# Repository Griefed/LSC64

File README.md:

# **This is still a WIP**

# **This is still a WIP**

# Sources, GitHub, GitLab and Mirroring and all that good stuff

Repositories on GitHub are now for issues only. I've set up my own installation of GitLab and moved all my repositories over to [Git.Griefed.de](https://git.griefed.de/users/Griefed/projects). Make sure to check there first for the latest code before opening an issue on GitHub.

For questions, you can always join my [Discord server](https://discord.griefed.de) and talk to me there.

---

[[_TOC_]]

**This has yet to be tested IRL. I currently don't have the funds to procure the PCB and parts in order to build and test it. No guarantee on anything as of yet. Also, the code for the Attiny85 has yet to be written, reason: See above.**
----
## Features

A PCB to enhance your C64C with various things:
- A Larson Scanner with RGB LEDs, so you can configure it to your liking!
- An Expansion Port reset circuit. You just need to connect a button and off you go!
- A CPU brake: Throttle your CPU and slow down your game during the really tricky bits!
- Mono & Stereo Headphone Amp. Listen to the beautiful SID sounds with your headphones. Either in mono or in stereo, if you have an FPGA SID!

## Assembly

After getting the PCB printed the the printing service of your choice and getting all the parts from the vendor of your choice, take a good look at [the interactive BOM](BOMinteractive.html).
It's a nice interactive overview of the whole PCB, which helps you placing all your parts where they're supposed to be! (You need to download )
Thanks to the Open Scope Project on GitHub for this amazing KiCad plugin: [InteractiveHtmlBom](https://github.com/openscopeproject/InteractiveHtmlBom)

## Connecting your LSC64

### Larson Scanner

For information about the pin layout of the power connector, check out: [C64 Power Supply Connector](https://www.c64-wiki.com/wiki/Power_Supply_Connector)

The bottom 3 pins of J1 to J20 are all the same. The top 3 pins of J1 to J20 represent one colour of the RGB LED each.
From left to right: red, blue green.
So, to set the colours of the LED:

| From                  | Of                   | To                        | Of                                                                                | Colour |
|:----------------------|:--------------------:|:-------------------------:|----------------------------------------------------------------------------------:|:------:|
| Any of J21            | LSC64                | Pin 5 (+5V DC)            | [C64 Power Supply Connector](https://www.c64-wiki.com/wiki/Power_Supply_Connector)| -x-    |
| Any of J21            | LSC64                | J24                       | LSC64                                                                             | -x-    |
| Any of J26            | LSC64                | Pin 2 (GND)               | [C64 Power Supply Connector](https://www.c64-wiki.com/wiki/Power_Supply_Connector)| -x-    |
| J1 to J20 - Bottom Row| LSC64                | J1 to J20 - Top Left      | LSC64                                                                             | Red    |
| J1 to J20 - Bottom Row| LSC64                | J1 to J20 - Top Middle    | LSC64                                                                             | Blue   |
| J1 to J20 - Bottom Row| LSC64                | J1 to J20 - Top Right     | LSC64                                                                             | Green  |

**Caution: Enabling more than one colour may result in the LED not lighting up at all. That is due to the output capacity of the Attiny85.**

**I recommend you only have one colour per LED enabled at all times.**

Special thanks to Luc Volders for the explanations and examples on how to build a charlieplexed Larson Scanner: [Luc's Tech Blog post about his Larson Scanner](https://lucstechblog.blogspot.com/2017/09/charlieplexing.html)

### The Reset Button

| From          | Of                   | To                        | Of                                                                                                      |
|:--------------|:--------------------:|:-------------------------:|--------------------------------------------------------------------------------------------------------:|
| J22           | LSC64                | Pin C (RESET)             | [C64 Expansion Port](https://www.c64-wiki.com/wiki/Expansion_Port)                                      |
| J27           | LSC64                | Pin 9 (EXROM)             | [C64 Expansion Port](https://www.c64-wiki.com/wiki/Expansion_Port)                                      |
| J23           | LSC64                | Pin 1                     | [Button](https://www.digikey.de/product-detail/de/e-switch/RP3502MABLK/EG1932-ND/280450?cur=EUR&lang=de)|
| Any of J26    | LSC64                | Pin 2                     | [Button](https://www.digikey.de/product-detail/de/e-switch/RP3502MABLK/EG1932-ND/280450?cur=EUR&lang=de)|

Special thanks to AntaBaka for the schematics and the idea: [Expansionport-Deluxe-Reset](http://pitsch.de/stuff/c64/index_c64.htm#A24)

### CPU Brake

| From          | Of                   | To                        | Of                                                                |
|:--------------|:--------------------:|:-------------------------:|------------------------------------------------------------------:|
| Pin 1         | On/Off Switch        | J21                       | LSC64                                                             |
| Pin 2         | On/Off Switch        | J24                       | LSC64                                                             |
| Terminal 1    | Dual Potentiometer   | Right Pin R29             | LSC64                                                             |
| Terminal 2    | Dual Potentiometer   | Middle Pin R29            | LSC64                                                             |
| Terminal 3    | Dual Potentiometer   | Left Pin R29              | LSC64                                                             |
| J25           | LSC64                | Pin 4 (IRQ)               | [C64 Expansion Port](https://www.c64-wiki.com/wiki/Expansion_Port)|

Special thanks to AntaBaka for the schematics and the idea: [CPU Brake NE555](http://pitsch.de/stuff/c64/index_c64.htm#A41)

### Mono-Stereo Headphone examples

##### CAUTION
- **Boards with assembly no. 250469 have no VR1. Check beforehand!**
- **Stereo sound REQUIRES an [FPGA SID](https://webstore.kryoflux.com/catalog/product_info.php?cPath=27&products_id=63&language=en)!**

| From          | Of                   | To                        | Of                                                         |
|:--------------|:--------------------:|:-------------------------:|-----------------------------------------------------------:|
| J31           | LSC64                | Pin 7 & 9                 | Rotary Switch                                              |
| J29           | LSC64                | Pin 2                     | Dual Potentiometer                                         |
| J35           | LSC64                | Pin 12                    | Rotary Switch                                              |
| J36           | LSC64                | Pin 5                     | Dual Potentiometer                                         |
| Pin 15 & 16   | Rotary Switch        | Pin 2                     | [VR1](images/Amp_Power_Supply.PNG)                         |
| Pin 1         | Dual Potentiometer   | Pin 3 (AUDIO_OUT)         | [C64 A/V connector](https://www.c64-wiki.com/wiki/A/V_Jack)|
| Pin 4         | Dual Potentiometer   | Pin 7 (FPGA SID AUDIO OUT)| [C64 A/V connector](https://www.c64-wiki.com/wiki/A/V_Jack)|
| Pin 3 & 6     | Dual Potentiometer   | Any of J26                | LSC64                                                      |
| J32           | LSC64                | Pin 13                    | Rotary Switch                                              |
| J38           | LSC64                | Pin 14                    | Rotary Switch                                              |
| Pin 1         | Rotary Switch        | Pin 2 (Tip) & Pin 3 (Ring)| Headphone Jack Mono                                        |
| Pin 1 (Sleeve)| Headphone Jack Mono  | Any of J26                | LSC64                                                      |
| Pin 3         | Rotary Switch        | Pin 2 (Tip)               | Headphone Jack Stereo                                      |
| Pin 6         | Rotary Switch        | Pin 3 (Ring)              | Headphone Jack Stereo                                      |
| Pin 1 (Sleeve)| Headphone Jack Stereo| Any of J26                | LSC64                                                      |

**Additional parts required but not listed in the InteractiveHtmlBom (They're not a physical part of the LSC64 PCB)**
- **4x3 rotary switch** (e.g.:[Symbol](images/Rotary_Switch4x3.PNG), [Datasheet Model A403](https://dznh3ojzb2azq.cloudfront.net/products/Rotary/A/documents/datasheet.pdf), [Product page](https://www.digikey.de/product-detail/de/c-k/A40315RNZQ/CKC7008-ND/181440)).
- **dual potentiometer to change the volume** (e.g.:[Symbol](images/Dual_Potentiometer.PNG), [Datasheet](https://www.bourns.com/docs/Product-Datasheets/PDB18.pdf), [Product page](https://www.digikey.de/product-detail/de/bourns-inc/PDB182-K430K-104A/PDB182-K430K-104A-ND/3780721)).
- **Audio jack to plug in your headphones** (e.g.: [Datasheet](https://us.schurter.com/bundles/snceschurter/epim/_ProdPool_/newDS/en/typ_4832.2300.pdf), [Product page](https://www.digikey.de/product-detail/de/schurter-inc/4832-2300/486-3419-ND/1731055)).

Special thanks to AntaBaka for the schematics and the idea [Headphone Amp Mono](http://pitsch.de/stuff/c64/index_amp.htm) and Minidisc.org for the stereo schematics [HeadBanger Headphone Amp](http://www.minidisc.org/headbanger.html)

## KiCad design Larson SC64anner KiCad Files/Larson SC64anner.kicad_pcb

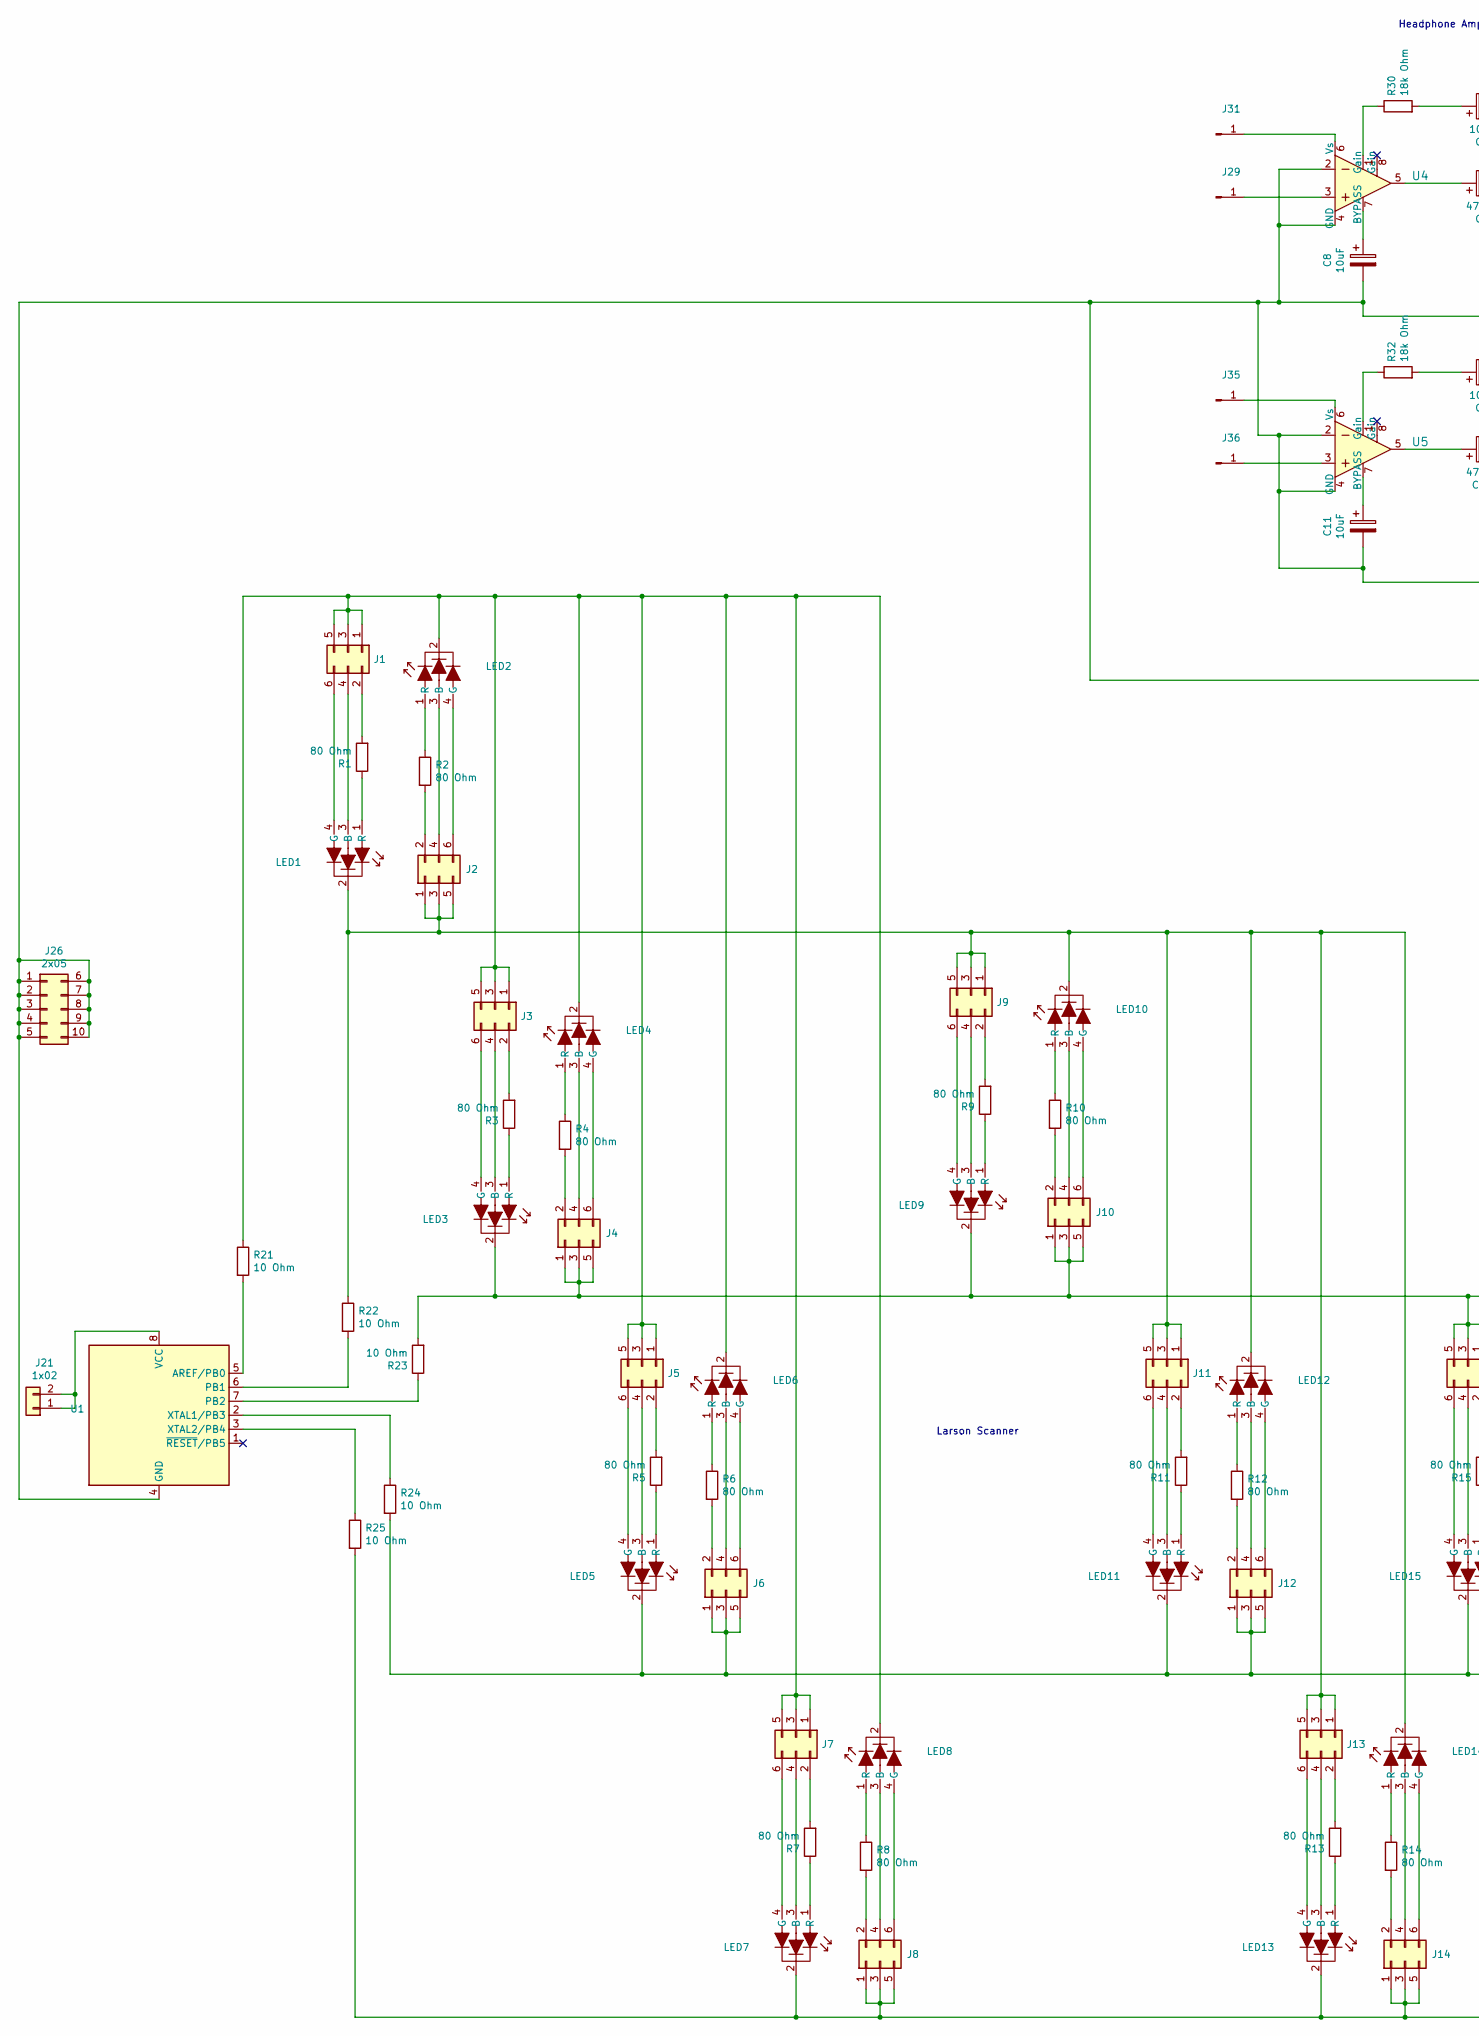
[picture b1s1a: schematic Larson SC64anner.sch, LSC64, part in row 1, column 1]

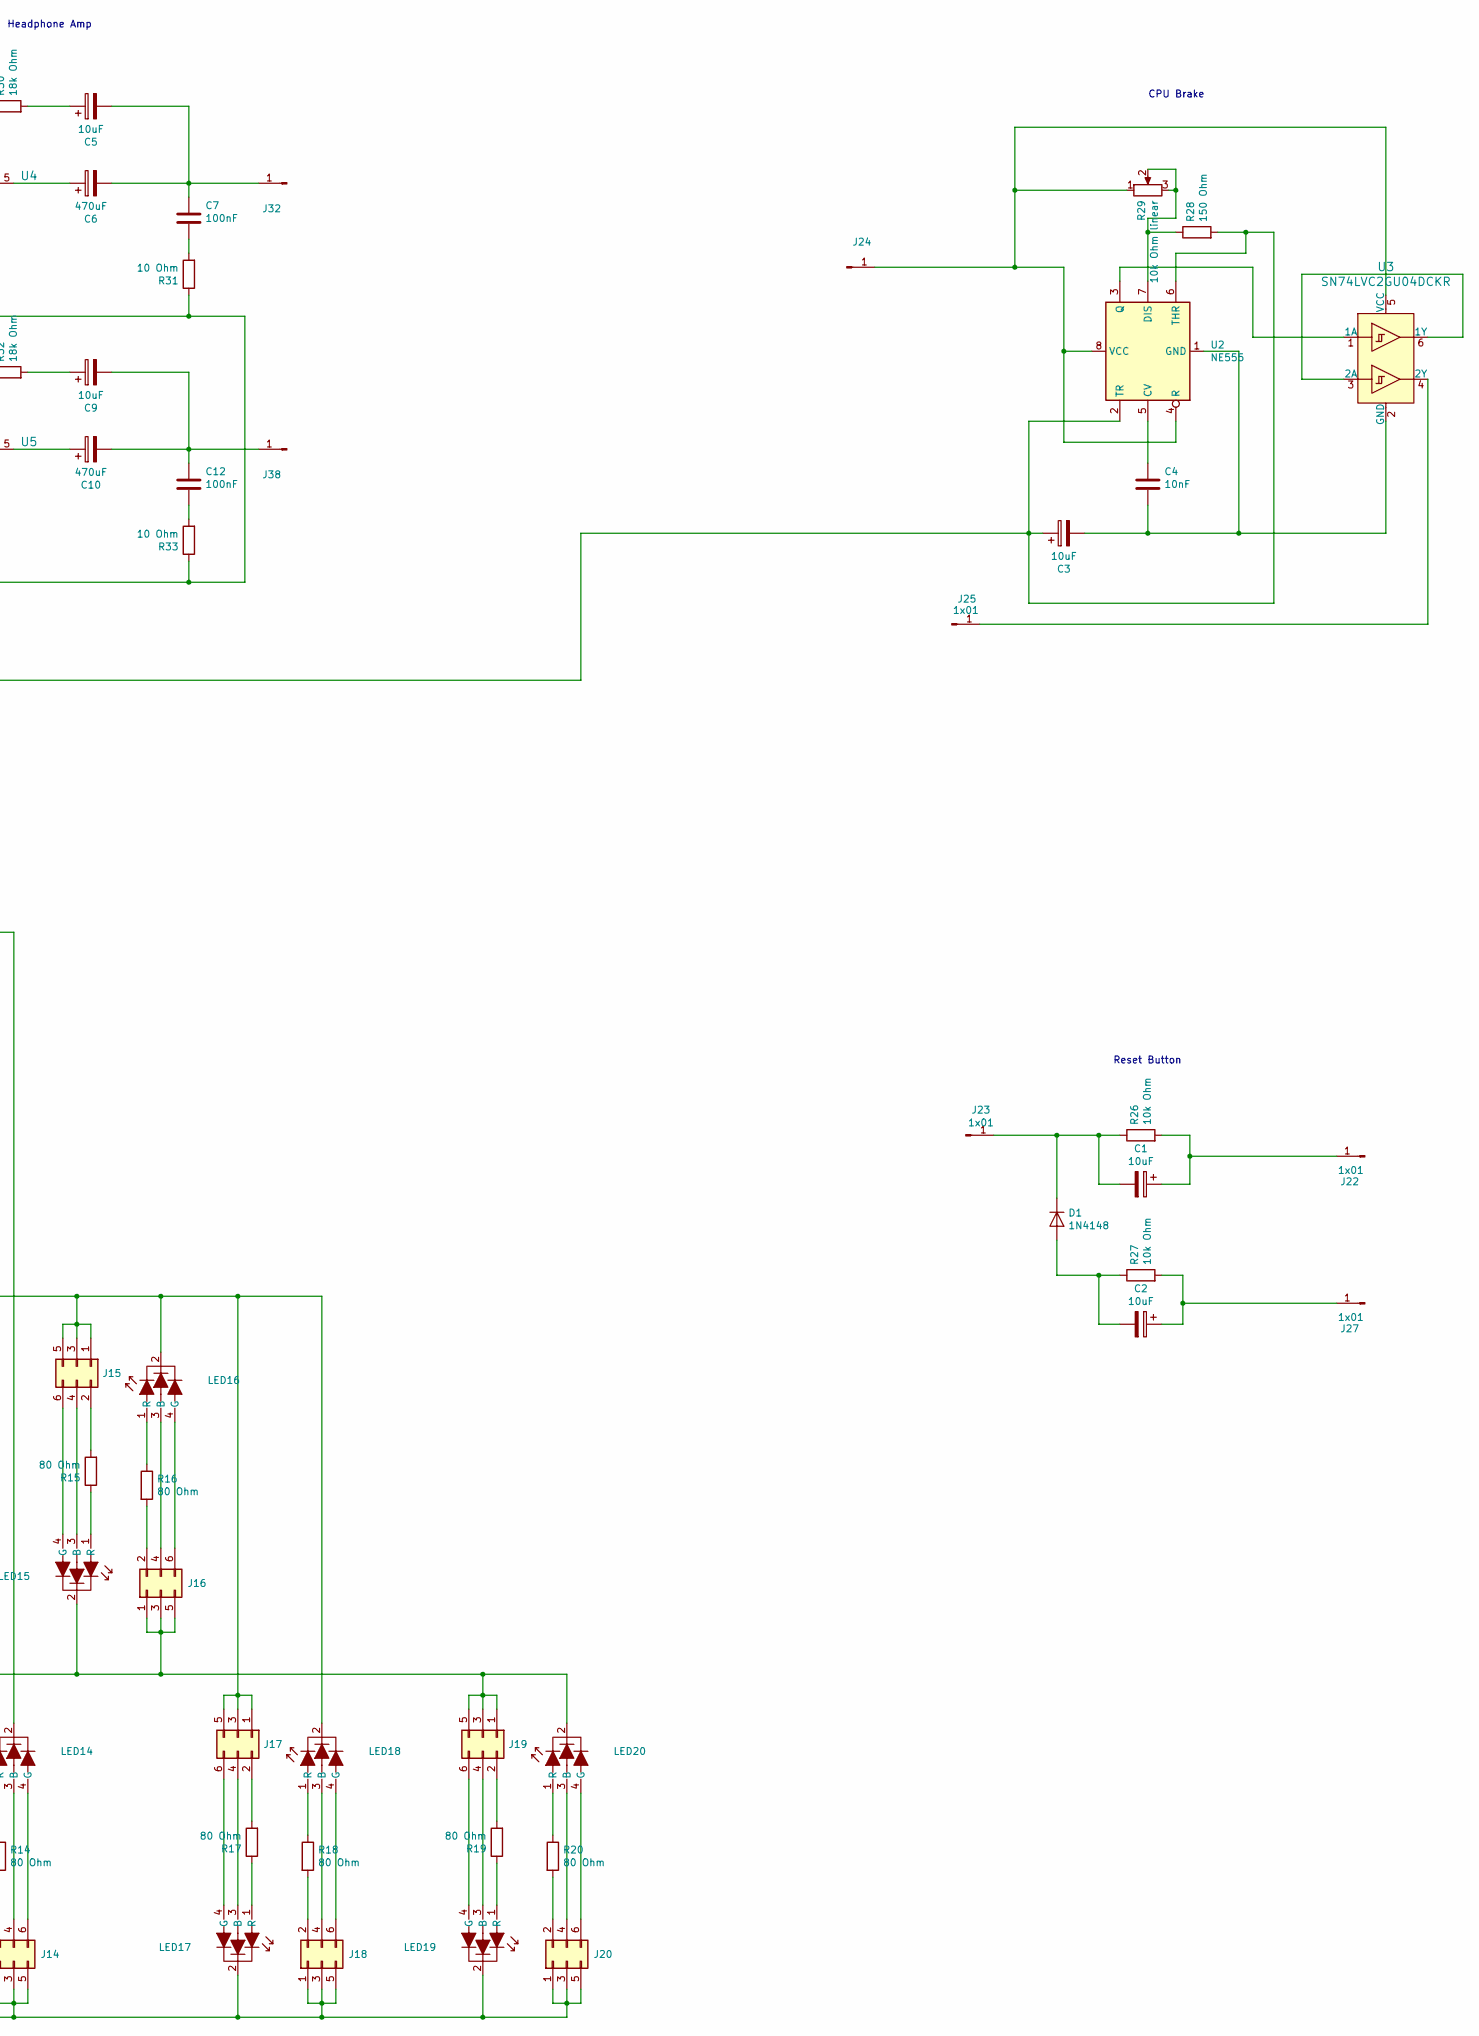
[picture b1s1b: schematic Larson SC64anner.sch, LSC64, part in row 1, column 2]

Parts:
C1, C2, C3, C5, C8, C9, C11: 10uF; CP_Radial_D5.0mm_P2.50mm
C4: 10nF; C_Disc_D7.5mm_W2.5mm_P5.00mm
C6, C10: 470uF; CP_Radial_D5.0mm_P2.50mm
C7, C12: 100nF; C_Disc_D7.5mm_W2.5mm_P5.00mm
D1: 1N4148; D_DO-35_SOD27_P7.62mm_Horizontal
J1, J2, J3, J4, J5, J6, J7, J8, J9, J10, J11, J12, J13, J14, J15, J16, J17, J18, J19, J20: 2x03; PinHeader_2x03_P2.54mm_Vertical
J21: 1x02; PinHeader_1x02_P2.54mm_Vertical
J22, J23, J24, J25, J27, J29, J31, J32, J35, J36, J38: 1x01; PinHeader_1x01_P2.54mm_Vertical
J26: 2x05; PinHeader_2x05_P2.54mm_Vertical
LED1, LED2, LED3, LED4, LED5, LED6, LED7, LED8, LED9, LED10, LED11, LED12, LED13, LED14, LED15, LED16, LED17, LED18, LED19, LED20: LED_CRGB; LED_RGB_WP154A4SUREQBFZGC
R1, R2, R3, R4, R5, R6, R7, R8, R9, R10, R11, R12, R13, R14, R15, R16, R17, R18, R19, R20: 80 Ohm; R_Axial_DIN0207_L6.3mm_D2.5mm_P2.54mm_Vertical_reduced_cour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
R21, R22, R23, R24, R25, R31, R33: 10 Ohm; R_Axial_DIN0207_L6.3mm_D2.5mm_P2.54mm_Vertical_reduced_cour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
R26, R27: 10k Ohm; R_Axial_DIN0207_L6.3mm_D2.5mm_P2.54mm_Vertical_reduced_cour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
R28: 150 Ohm; R_Axial_DIN0207_L6.3mm_D2.5mm_P2.54mm_Vertical_reduced_cour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
R29: 10k Ohm linear; PinHeader_1x03_P2.54mm_Vertical
R30, R32: 18k Ohm; R_Axial_DIN0207_L6.3mm_D2.5mm_P2.54mm_Vertical_reduced_cour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
U1: ATtiny85V-20PU; DIP-8_W7.62mm
U2: NE555; DIP-8_W7.62mm
U3: SN74LVC2GU04DCKR; SMDIP-6_W7.62mm
U4, U5: LM386N-4_NOPB; DIP-8_W7.62mm; MPN LM386N-4/NOPB; Digi-Key_PN 296-43960-5-ND

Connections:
unnamed: C1.1, J22.1, R26.2
unnamed: C1.2, D1.1 (K), J23.1, R26.1
unnamed: C2.1, J27.1, R27.2
unnamed: C2.2, D1.2 (A), R27.1
unnamed: C3.2, C4.2, U2.1 (GND), U3.2 (GND)
unnamed: C4.1, U2.5 (CV)
unnamed: C5.1, R30.2
unnamed: C5.2, C6.2, C7.1, J32.1
unnamed: C6.1, U4.5
unnamed: C7.2, R31.2
unnamed: C8.1, U4.7 (BYPASS)
unnamed: C9.1, R32.2
unnamed: C10.1, U5.5
unnamed: C9.2, C10.2, C12.1, J38.1
unnamed: C11.1, U5.7 (BYPASS)
unnamed: C3.1, C8.2, C11.2, J26.1, J26.2, J26.3, J26.4, J26.5, J26.6, J26.7, J26.8, J26.9, J26.10, R28.2, R31.1, R33.1, U1.4 (GND), U2.2 (TR), U2.6 (THR), U4.2, U4.4 (GND), U5.2, U5.4 (GND)
unnamed: C12.2, R33.2
unnamed: J1.1, J1.3, J1.5, J3.1, J3.3, J3.5, J5.1, J5.3, J5.5, J7.1, J7.3, J7.5, LED2.2, LED4.2, LED6.2, LED8.2, R21.1
unnamed: J1.2, R1.2
unnamed: J1.4, LED1.3 (B)
unnamed: J1.6, LED1.4 (G)
unnamed: J2.2, R2.2
unnamed: J2.4, LED2.3 (B)
unnamed: J2.6, LED2.4 (G)
unnamed: J3.2, R3.2
unnamed: J3.4, LED3.3 (B)
unnamed: J3.6, LED3.4 (G)
unnamed: J4.2, R4.2
unnamed: J4.4, LED4.3 (B)
unnamed: J4.6, LED4.4 (G)
unnamed: J5.2, R5.2
unnamed: J5.4, LED5.3 (B)
unnamed: J5.6, LED5.4 (G)
unnamed: J6.2, R6.2
unnamed: J6.4, LED6.3 (B)
unnamed: J6.6, LED6.4 (G)
unnamed: J7.2, R7.2
unnamed: J7.4, LED7.3 (B)
unnamed: J7.6, LED7.4 (G)
unnamed: J8.2, R8.2
unnamed: J8.4, LED8.3 (B)
unnamed: J8.6, LED8.4 (G)
unnamed: J9.2, R9.2
unnamed: J9.4, LED9.3 (B)
unnamed: J9.6, LED9.4 (G)
unnamed: J4.1, J4.3, J4.5, J10.1, J10.3, J10.5, J15.1, J15.3, J15.5, J17.1, J17.3, J17.5, LED3.2, LED9.2, LED16.2, LED18.2, R23.2
unnamed: J10.2, R10.2
unnamed: J10.4, LED10.3 (B)
unnamed: J10.6, LED10.4 (G)
unnamed: J2.1, J2.3, J2.5, J9.1, J9.3, J9.5, J11.1, J11.3, J11.5, J13.1, J13.3, J13.5, LED1.2, LED10.2, LED12.2, LED14.2, R22.1
unnamed: J11.2, R11.2
unnamed: J11.4, LED11.3 (B)
unnamed: J11.6, LED11.4 (G)
unnamed: J6.1, J6.3, J6.5, J12.1, J12.3, J12.5, J16.1, J16.3, J16.5, J19.1, J19.3, J19.5, LED5.2, LED11.2, LED15.2, LED20.2, R24.2
unnamed: J12.2, R12.2
unnamed: J12.4, LED12.3 (B)
unnamed: J12.6, LED12.4 (G)
unnamed: J13.2, R13.2
unnamed: J13.4, LED13.3 (B)
unnamed: J13.6, LED13.4 (G)
unnamed: J8.1, J8.3, J8.5, J14.1, J14.3, J14.5, J18.1, J18.3, J18.5, J20.1, J20.3, J20.5, LED7.2, LED13.2, LED17.2, LED19.2, R25.2
unnamed: J14.2, R14.2
unnamed: J14.4, LED14.3 (B)
unnamed: J14.6, LED14.4 (G)
unnamed: J15.2, R15.2
unnamed: J15.4, LED15.3 (B)
unnamed: J15.6, LED15.4 (G)
unnamed: J16.2, R16.2
unnamed: J16.4, LED16.3 (B)
unnamed: J16.6, LED16.4 (G)
unnamed: J17.2, R17.2
unnamed: J17.4, LED17.3 (B)
unnamed: J17.6, LED17.4 (G)
unnamed: J18.2, R18.2
unnamed: J18.4, LED18.3 (B)
unnamed: J18.6, LED18.4 (G)
unnamed: J19.2, R19.2
unnamed: J19.4, LED19.3 (B)
unnamed: J19.6, LED19.4 (G)
unnamed: J20.2, R20.2
unnamed: J20.4, LED20.3 (B)
unnamed: J20.6, LED20.4 (G)
unnamed: J21.1, J21.2, U1.8 (VCC)
unnamed: J24.1, R29.1, U2.4 (R), U2.8 (VCC), U3.5 (VCC)
unnamed: J25.1, U3.4 (2Y)
unnamed: J29.1, U4.3
unnamed: J31.1, U4.6 (Vs)
unnamed: J35.1, U5.6 (Vs)
unnamed: J36.1, U5.3
unnamed: LED1.1 (R), R1.1
unnamed: LED2.1 (R), R2.1
unnamed: LED3.1 (R), R3.1
unnamed: LED4.1 (R), R4.1
unnamed: LED5.1 (R), R5.1
unnamed: LED6.1 (R), R6.1
unnamed: LED7.1 (R), R7.1
unnamed: LED8.1 (R), R8.1
unnamed: LED9.1 (R), R9.1
unnamed: LED10.1 (R), R10.1
unnamed: LED11.1 (R), R11.1
unnamed: LED12.1 (R), R12.1
unnamed: LED13.1 (R), R13.1
unnamed: LED14.1 (R), R14.1
unnamed: LED15.1 (R), R15.1
unnamed: LED16.1 (R), R16.1
unnamed: LED17.1 (R), R17.1
unnamed: LED18.1 (R), R18.1
unnamed: LED19.1 (R), R19.1
unnamed: LED20.1 (R), R20.1
unnamed: R21.2, U1.5 (AREF/PB0)
unnamed: R22.2, U1.6 (PB1)
unnamed: R23.1, U1.7 (PB2)
unnamed: R24.1, U1.2 (XTAL1/PB3)
unnamed: R25.1, U1.3 (XTAL2/PB4)
unnamed: R28.1, R29.2, R29.3, U2.7 (DIS)
unnamed: R30.1, U4.1 (Gain)
unnamed: R32.1, U5.1 (Gain)
unnamed: U2.3 (Q), U3.1 (1A)
unnamed: U3.3 (2A), U3.6 (1Y)

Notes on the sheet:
Reset Button
CPU Brake
Headphone Amp
Larson Scanner

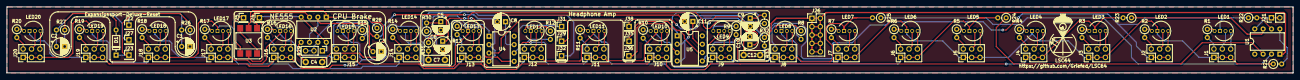
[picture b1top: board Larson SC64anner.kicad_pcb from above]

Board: 2 copper layers, 390.0 x 20.0 mm, 104 parts (0 on the bottom side), 119 nets.

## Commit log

2020-03-21 Add files via upload
    KiCad files for the PCB, schematic, netlist etc. etc.
2020-03-21 Add files via upload
    KiCad library footprint and symbol files needed for the schematic and pcb
2020-03-26 no message
2020-03-28 Updated PCB
    - Touchups
    - Added mono / stereo headphone amp circuitry
2020-03-28 Updated ibom.html
    Updated bill of materials
2020-03-28 Cleand up Silk-Layer
    Minor beauty corrections
2020-03-28 Starting work on amp documentation
    Added screenshot of pcb part
    Edited README with additional information
2020-03-28 Added logo as well as a smal version
2020-03-28 Cleanup and documentation
    - Deleted some unnecessary parts
    - Started description on how to connect the headphone amp circuitry
2020-03-29 misc
2020-03-29 Changed folder structure
2020-03-29 Updated README, BOMinteractive and Mono-Stereo-Headphone-Amp.PNG
2020-03-29 Added Social Preview image
2020-03-29 Updated Social Preview and added source if you want to change it, too
2020-03-29 Changed file structure, cleaned the place up a bit
2020-03-29 PCB cleanup
2020-03-29 Update Larson SC64anner.kicad_pcb-bak
2020-03-29 Cleaned up front silk layer
2020-03-30 Re-arrange headphone amp circtuit
    Re-did and re-arranged the whole headphone amp circuitry into a more orderly fashion.
2020-04-02 Updated PCB, README, Schmetic
    Simpliefied things a bit.
2020-04-03 Updated README
    Switched the description of the connections from stupid text lists to tables. Much better!
2020-04-03 Cleanup and corrections
    Cleaned up the pcb a bit and made new screenshots.
    Also fixed some more minor things in the README. Will it ever end? :D
2020-04-03 Gerber Files
    Changed some settings of the gerber job files to fit PCBWay settings.
2020-04-03 Update README.md
    Forgot to add the connection to ground. Whoops.
2020-04-04 Create sketch_apr04a.ino
    Started working on the Larscon Scanner code
2020-04-04 Various
    -Added a sociel preview with the LED part of the schematic in the background
    -Filled the unsued zones of the pcb with copper fields, to increase production quality due to equal spread of copper layers (galvanic index)
2020-04-04 Update README.md
    Fixed small typo
2020-04-04 Updated Previews for README
2020-04-05 Updated PCB
    -Cleaned up the silklayer which resulted in redoing screenshots and gerber files etc.
2020-04-10 Minor touchups
2020-04-10 More cleanups
    Cleaned the PCB up some more.
2020-04-10 Tests
2020-04-11 More cleanups
2020-10-06 Update README.md
    Changed **This is still a WIP** to # for better visibility.
2020-10-06 Create LICENSE
2020-10-07 Update fp-info-cache
2021-06-26 chore: Inform users/visitors about move to GitLab
2021-07-14 chore: Add GitLab issue templates
